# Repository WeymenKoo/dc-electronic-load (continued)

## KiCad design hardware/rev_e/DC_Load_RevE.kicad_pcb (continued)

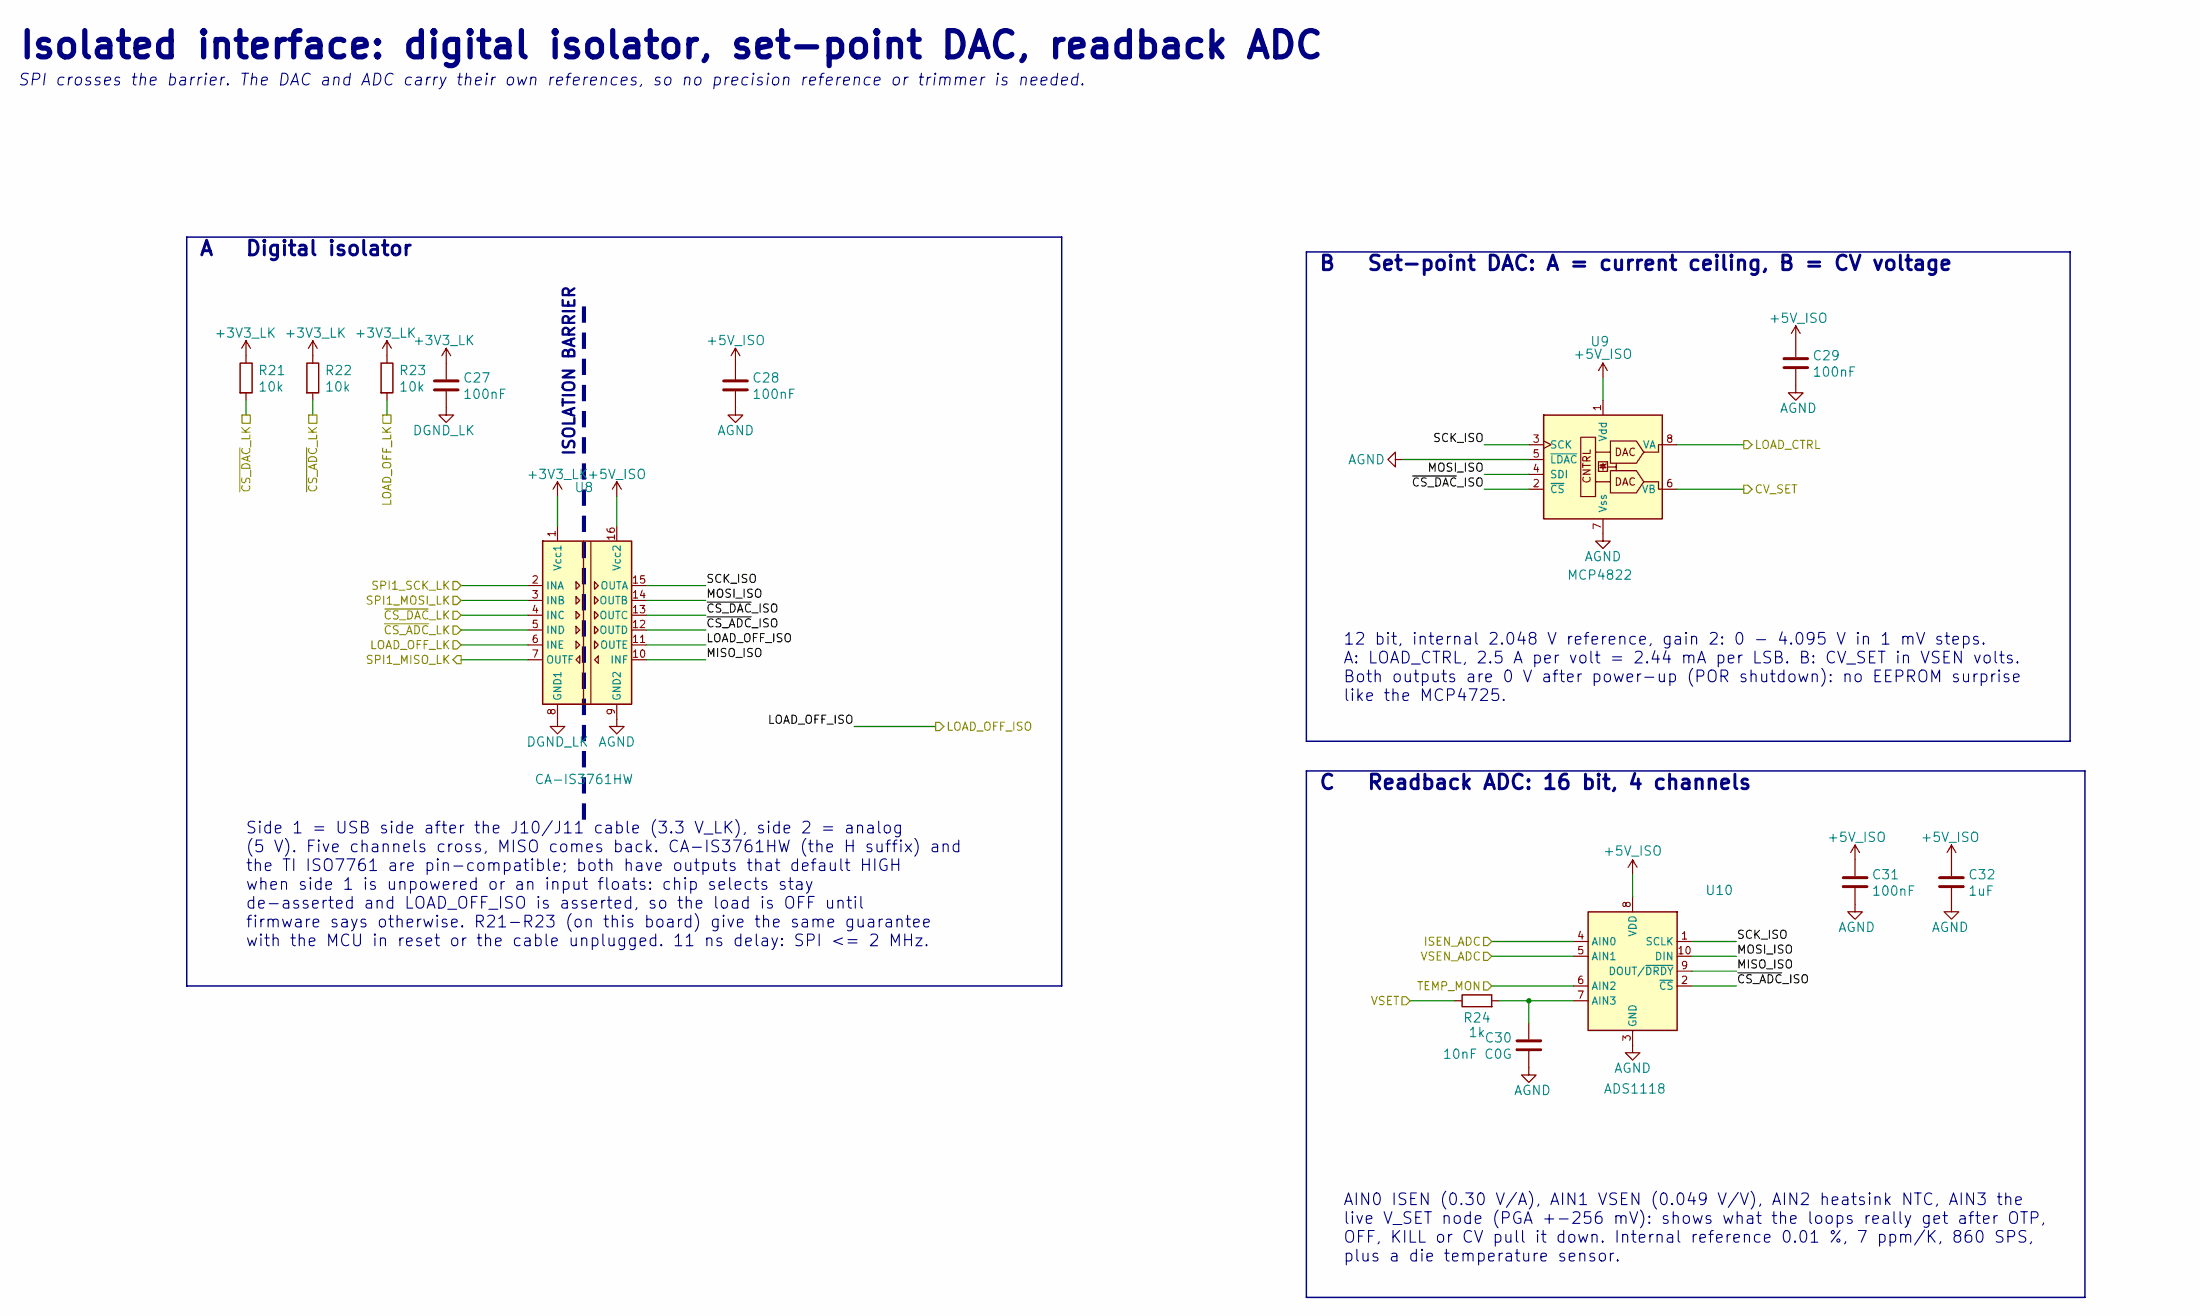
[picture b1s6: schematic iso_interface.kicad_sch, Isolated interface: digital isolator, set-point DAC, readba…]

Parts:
C27, C28, C29, C31: 100nF; C_0603_1608Metric
C30: 10nF C0G; C_0603_1608Metric
C32: 1uF; C_0603_1608Metric
R21, R22, R23: 10k; R_0603_1608Metric
R24: 1k; R_0603_1608Metric
U8: CA-IS3761HW; SOIC-16W_7.5x10.3mm_P1.27mm; MPN Chipanalog CA-IS3761HW, 5 kVrms, defaul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; LCSC C528656
U9: MCP4822; SOIC-8_3.9x4.9mm_P1.27mm; MPN MCP4822-E/SN; LCSC C16040
U10: ADS1118; TSSOP-10_3x3mm_P0.5mm; MPN ADS1118IDGSR; LCSC C55347

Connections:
+3V3_LK: C27.1, R21.1, R22.1, R23.1, U8.1 (Vcc1); also elsewhere on the board
+5V_ISO: C28.1, C29.1, C31.1, C32.1, U8.16 (Vcc2), U9.1 (Vdd), U10.8 (VDD); also elsewhere on the board
/Board Link/LOAD_OFF_LK: R23.2, U8.6 (INE); also elsewhere on the board
/Board Link/SPI1_MISO_LK: U8.7 (OUTF); also elsewhere on the board
/Board Link/SPI1_MOSI_LK: U8.3 (INB); also elsewhere on the board
/Board Link/SPI1_SCK_LK: U8.2 (INA); also elsewhere on the board
/Board Link/~CS_ADC_LK: R22.2, U8.5 (IND); also elsewhere on the board
/Board Link/~CS_DAC_LK: R21.2, U8.4 (INC); also elsewhere on the board
/Channel 1/VSET: R24.1; also elsewhere on the board
/Isolated Interface/CV_SET: U9.6 (VB); also elsewhere on the board
/Isolated Interface/ISEN_ADC: U10.4 (AIN0); also elsewhere on the board
/Isolated Interface/LOAD_CTRL: U9.8 (VA); also elsewhere on the board
/Isolated Interface/LOAD_OFF_ISO: U8.11 (OUTE); also elsewhere on the board
/Isolated Interface/MISO_ISO: U8.10 (INF), U10.9 (DOUT/~DRDY)
/Isolated Interface/MOSI_ISO: U8.14 (OUTB), U9.4 (SDI), U10.10 (DIN)
/Isolated Interface/SCK_ISO: U8.15 (OUTA), U9.3 (SCK), U10.1 (SCLK)
/Isolated Interface/TEMP_MON: U10.6 (AIN2); also elsewhere on the board
/Isolated Interface/VSEN_ADC: U10.5 (AIN1); also elsewhere on the board
/Isolated Interface/~CS_ADC_ISO: U8.12 (OUTD), U10.2 (~CS)
/Isolated Interface/~CS_DAC_ISO: U8.13 (OUTC), U9.2 (~CS)
AGND: C28.2, C29.2, C30.2, C31.2, C32.2, U8.9 (GND2), U9.5 (~LDAC), U9.7 (Vss), U10.3 (GND); also elsewhere on the board
DGND_LK: C27.2, U8.8 (GND1); also elsewhere on the board
unnamed: C30.1, R24.2, U10.7 (AIN3)

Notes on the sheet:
Isolated interface: digital isolator, set-point DAC, readback ADC
SPI crosses the barrier. The DAC and ADC carry their own references, so no precision reference or trimmer is needed.
ISOLATION BARRIER
Side 1 = USB side after the J10/J11 cable (3.3 V_LK), side 2 = analog (5 V). Five channels cross, MISO comes back. CA-IS3761HW (the H suffix) and the TI ISO7761 are pin-compatible; both have outputs that default HIGH when side 1 is unpowered or an input floats: chip selects stay de-asserted and LOA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
A Digital isolator
12 bit, internal 2.048 V reference, gain 2: 0 - 4.095 V in 1 mV steps. A: LOAD_CTRL, 2.5 A per volt = 2.44 mA per LSB. B: CV_SET in VSEN volts. Both outputs are 0 V after power-up (POR shutdown): no EEPROM surprise like the MCP4725.
B Set-point DAC: A = current ceiling, B = CV voltage
AIN0 ISEN (0.30 V/A), AIN1 VSEN (0.049 V/V), AIN2 heatsink NTC, AIN3 the live V_SET node (PGA +-256 mV): shows what the loops really get after OTP, OFF, KILL or CV pull it down. Internal reference 0.01 %, 7 ppm/K, 860 SPS, plus a die temperature sensor.
C Readback ADC: 16 bit, 4 channels

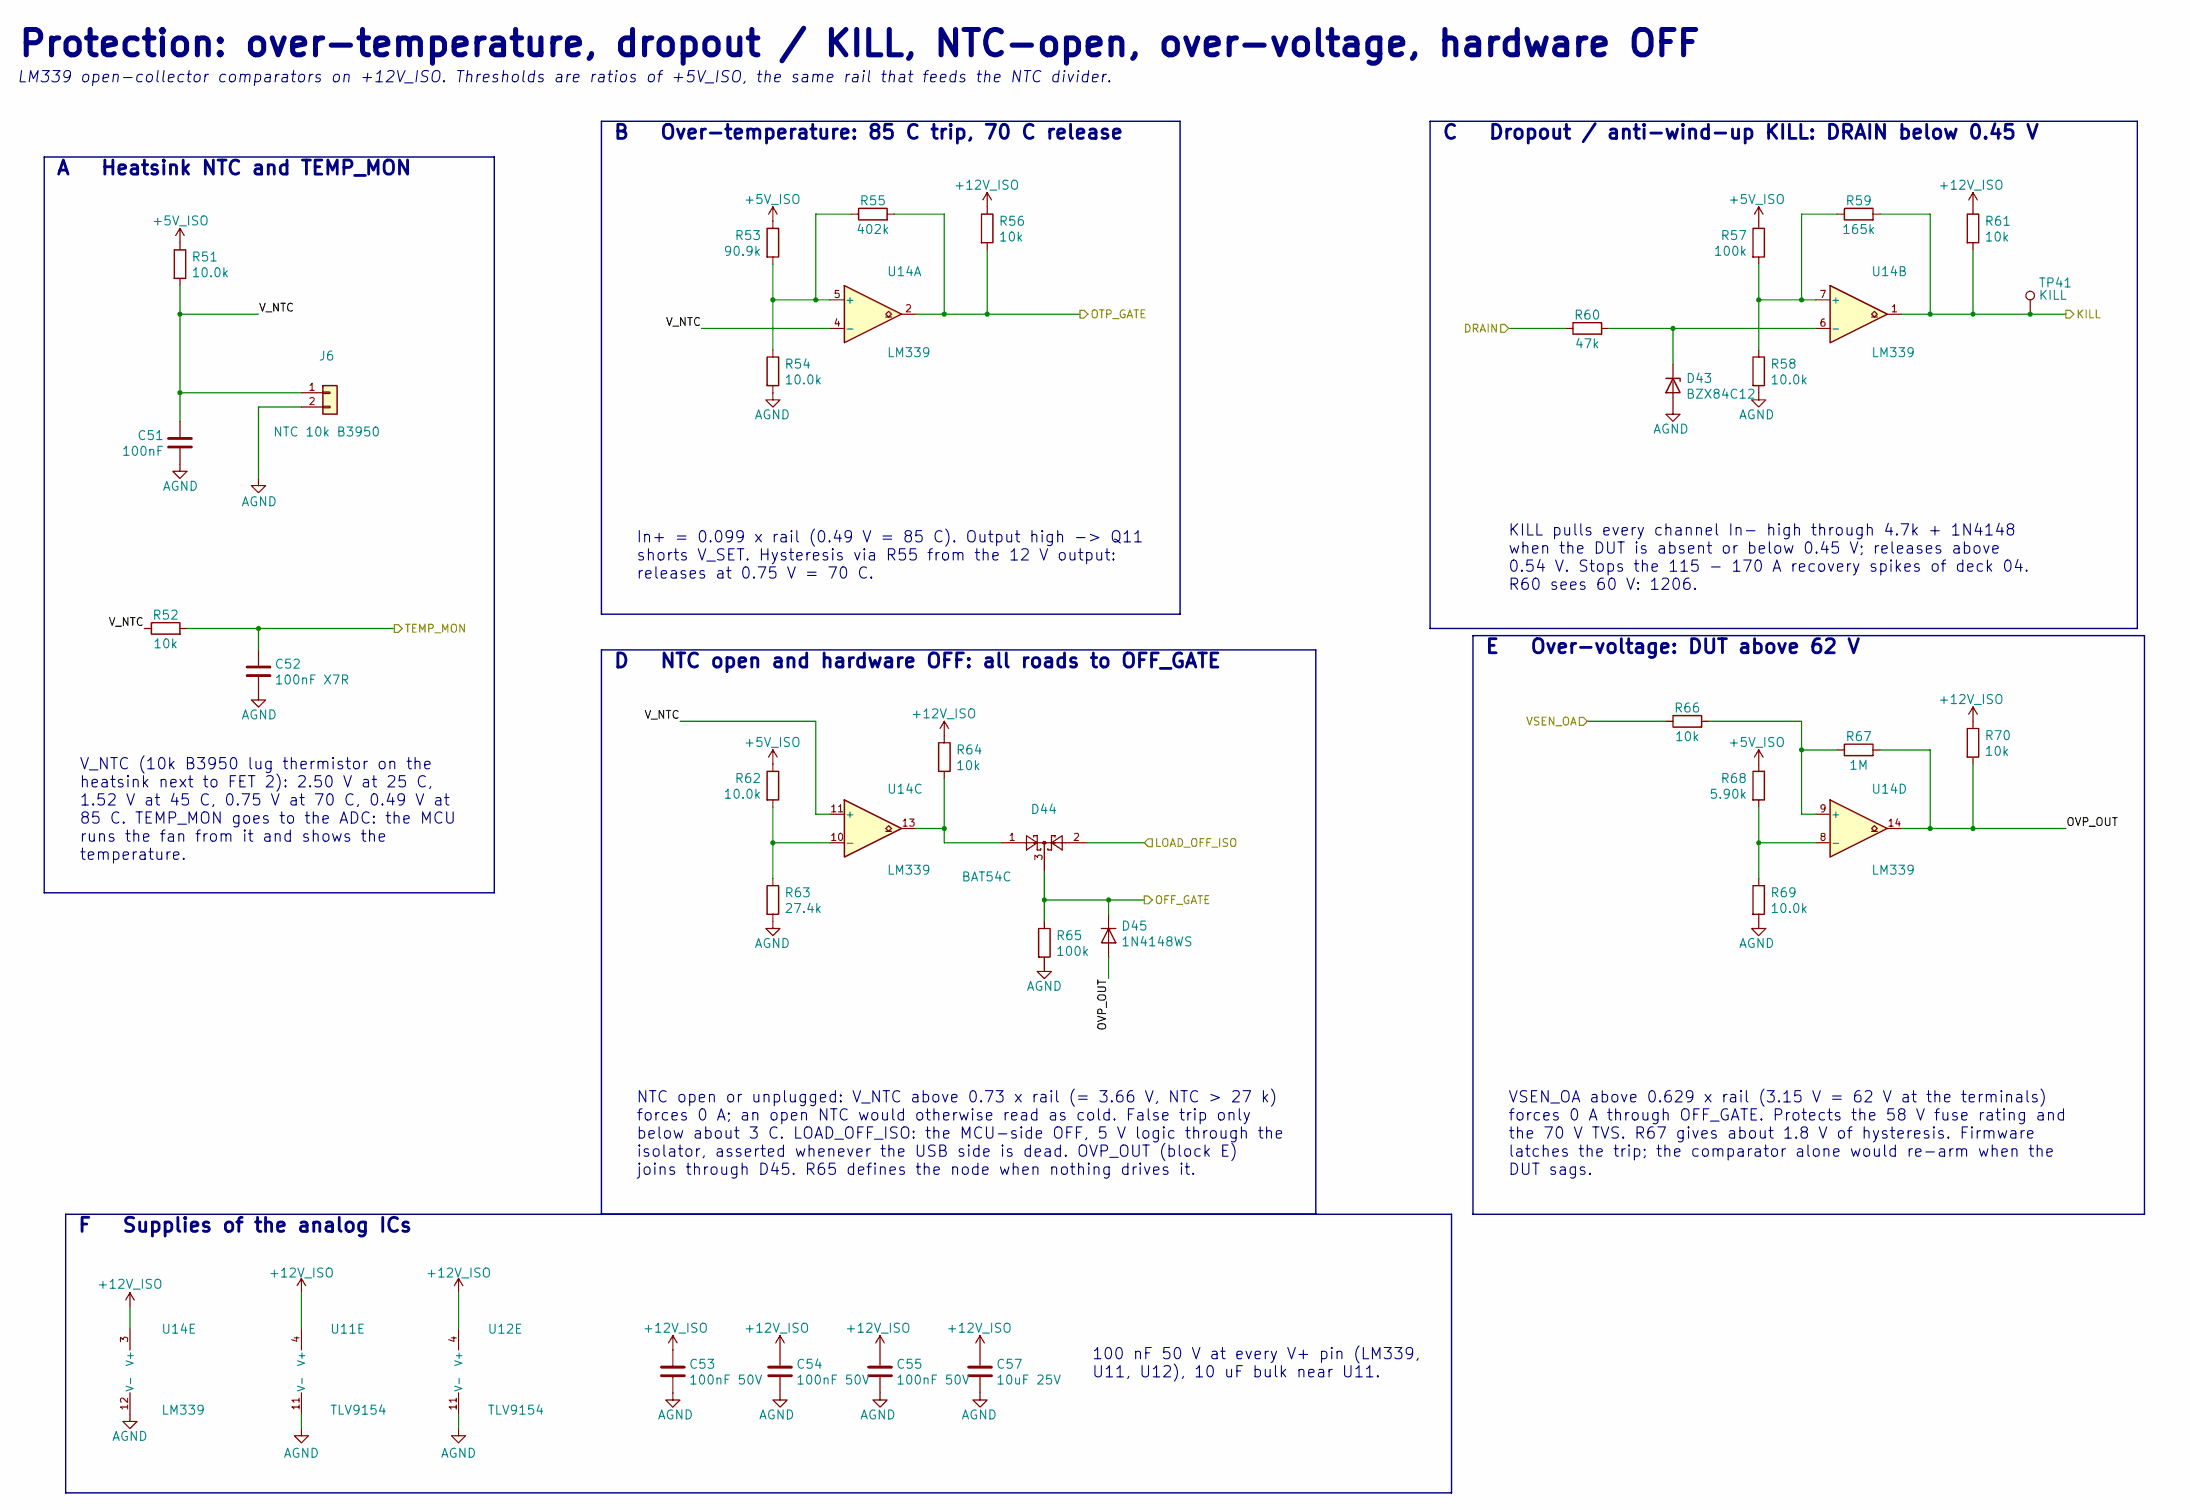
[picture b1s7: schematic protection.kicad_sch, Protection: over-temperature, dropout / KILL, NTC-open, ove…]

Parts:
C51: 100nF; C_0603_1608Metric
C52: 100nF X7R; C_0603_1608Metric
C53, C54, C55: 100nF 50V; C_0603_1608Metric
C57: 10uF 25V; C_0805_2012Metric
D43: BZX84C12; SOT-23; LCSC C118577
D44: BAT54C; SOT-23; LCSC C2135
D45: 1N4148WS; D_SOD-323; LCSC C2128
J6: NTC 10k B3950; JST_XH_B2B-XH-A_1x02_P2.50mm_Vertical; MPN JST B2B-XH-A(LF)(SN); NTC = 10k B3950 r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; LCSC C158012
R51, R54, R58, R62, R69: 10.0k; R_0603_1608Metric; Tolerance 1%
R52, R56, R61, R64, R70: 10k; R_0603_1608Metric
R53: 90.9k; R_0603_1608Metric; Tolerance 1%
R55: 402k; R_0603_1608Metric; Tolerance 1%
R57: 100k; R_0603_1608Metric; Tolerance 1%
R59: 165k; R_0603_1608Metric; Tolerance 1%
R60: 47k; R_1206_3216Metric; Tolerance 1%; LCSC C102201
R63: 27.4k; R_0603_1608Metric; Tolerance 1%
R65: 100k; R_0603_1608Metric
R66: 10k; R_0603_1608Metric; Tolerance 1%
R67: 1M; R_0603_1608Metric; Tolerance 1%
R68: 5.90k; R_0603_1608Metric; Tolerance 1%
TP41: KILL; TestPoint_THTPad_D1.5mm_Drill0.7mm
U11, U12: TLV9154; SOIC-14_3.9x8.7mm_P1.27mm; MPN TLV9154IDR; LCSC C2873614
U14: LM339; SOIC-14_3.9x8.7mm_P1.27mm; MPN LM339DR; LCSC C5236695

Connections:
+5V_ISO: R51.1, R53.1, R57.1, R62.1, R68.1; also elsewhere on the board
+12V_ISO: C53.1, C54.1, C55.1, C57.1, R56.1, R61.1, R64.1, R70.1, U11.4 (V+), U12.4 (V+), U14.3 (V+); also elsewhere on the board
/Channel 1/DRAIN: R60.1; also elsewhere on the board
/Channel 1/KILL: R59.2, R61.2, TP41.1, U14.1; also elsewhere on the board
/Channel 1/VSET: U11.5 (+), U11.10 (+), U11.12 (+); also elsewhere on the board
/Isolated Interface/LOAD_OFF_ISO: D44.2; also elsewhere on the board
/Isolated Interface/TEMP_MON: C52.1, R52.2; also elsewhere on the board
/Protection/OFF_GATE: D44.3, D45.1 (K), R65.1; also elsewhere on the board
/Protection/OTP_GATE: R55.2, R56.2, U14.2; also elsewhere on the board
/Protection/OVP_OUT: D45.2 (A), R67.2, R70.2, U14.14
/Protection/VSEN_OA: R66.1; also elsewhere on the board
/Protection/V_NTC: C51.1, J6.1, R51.2, R52.1, U14.4 (-), U14.11 (+)
AGND: C51.2, C52.2, C53.2, C54.2, C55.2, C57.2, D43.1 (A), J6.2, R54.2, R58.2, R63.2, R65.2, R69.2, U11.11 (V-), U12.11 (V-), U14.12 (V-); also elsewhere on the board
unnamed: D43.3 (K), R60.2, U14.6 (-)
unnamed: D44.1, R64.2, U14.13
unnamed 82: U11.6 (-); also elsewhere on the board
unnamed 83: U11.7; also elsewhere on the board
unnamed 87: U11.9 (-); also elsewhere on the board
unnamed 88: U11.8; also elsewhere on the board
unnamed 92: U11.13 (-); also elsewhere on the board
unnamed 93: U11.14; also elsewhere on the board
unnamed: R53.2, R54.1, R55.1, U14.5 (+)
unnamed: R57.2, R58.1, R59.1, U14.7 (+)
unnamed: R62.2, R63.1, U14.10 (-)
unnamed: R66.2, R67.1, U14.9 (+)
unnamed: R68.2, R69.1, U14.8 (-)

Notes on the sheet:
Protection: over-temperature, dropout / KILL, NTC-open, over-voltage, hardware OFF
LM339 open-collector comparators on +12V_ISO. Thresholds are ratios of +5V_ISO, the same rail that feeds the NTC divider.
V_NTC (10k B3950 lug thermistor on the heatsink next to FET 2): 2.50 V at 25 C, 1.52 V at 45 C, 0.75 V at 70 C, 0.49 V at 85 C. TEMP_MON goes to the ADC: the MCU runs the fan from it and shows the temperature.
A Heatsink NTC and TEMP_MON
In+ = 0.099 x rail (0.49 V = 85 C). Output high -> Q11 shorts V_SET. Hysteresis via R55 from the 12 V output: releases at 0.75 V = 70 C.
B Over-temperature: 85 C trip, 70 C release
KILL pulls every channel In- high through 4.7k + 1N4148 when the DUT is absent or below 0.45 V; releases above 0.54 V. Stops the 115 - 170 A recovery spikes of deck 04. R60 sees 60 V: 1206.
C Dropout / anti-wind-up KILL: DRAIN below 0.45 V
NTC open or unplugged: V_NTC above 0.73 x rail (= 3.66 V, NTC > 27 k) forces 0 A; an open NTC would otherwise read as cold. False trip only below about 3 C. LOAD_OFF_ISO: the MCU-side OFF, 5 V logic through the isolator, asserted whenever the USB side is dead. OVP_OUT (block E) joins through D45. R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
D NTC open and hardware OFF: all roads to OFF_GATE
VSEN_OA above 0.629 x rail (3.15 V = 62 V at the terminals) forces 0 A through OFF_GATE. Protects the 58 V fuse rating and the 70 V TVS. R67 gives about 1.8 V of hysteresis. Firmware latches the trip; the comparator alone would re-arm when the DUT sags.
E Over-voltage: DUT above 62 V
100 nF 50 V at every V+ pin (LM339, U11, U12), 10 uF bulk near U11.
F Supplies of the analog ICs

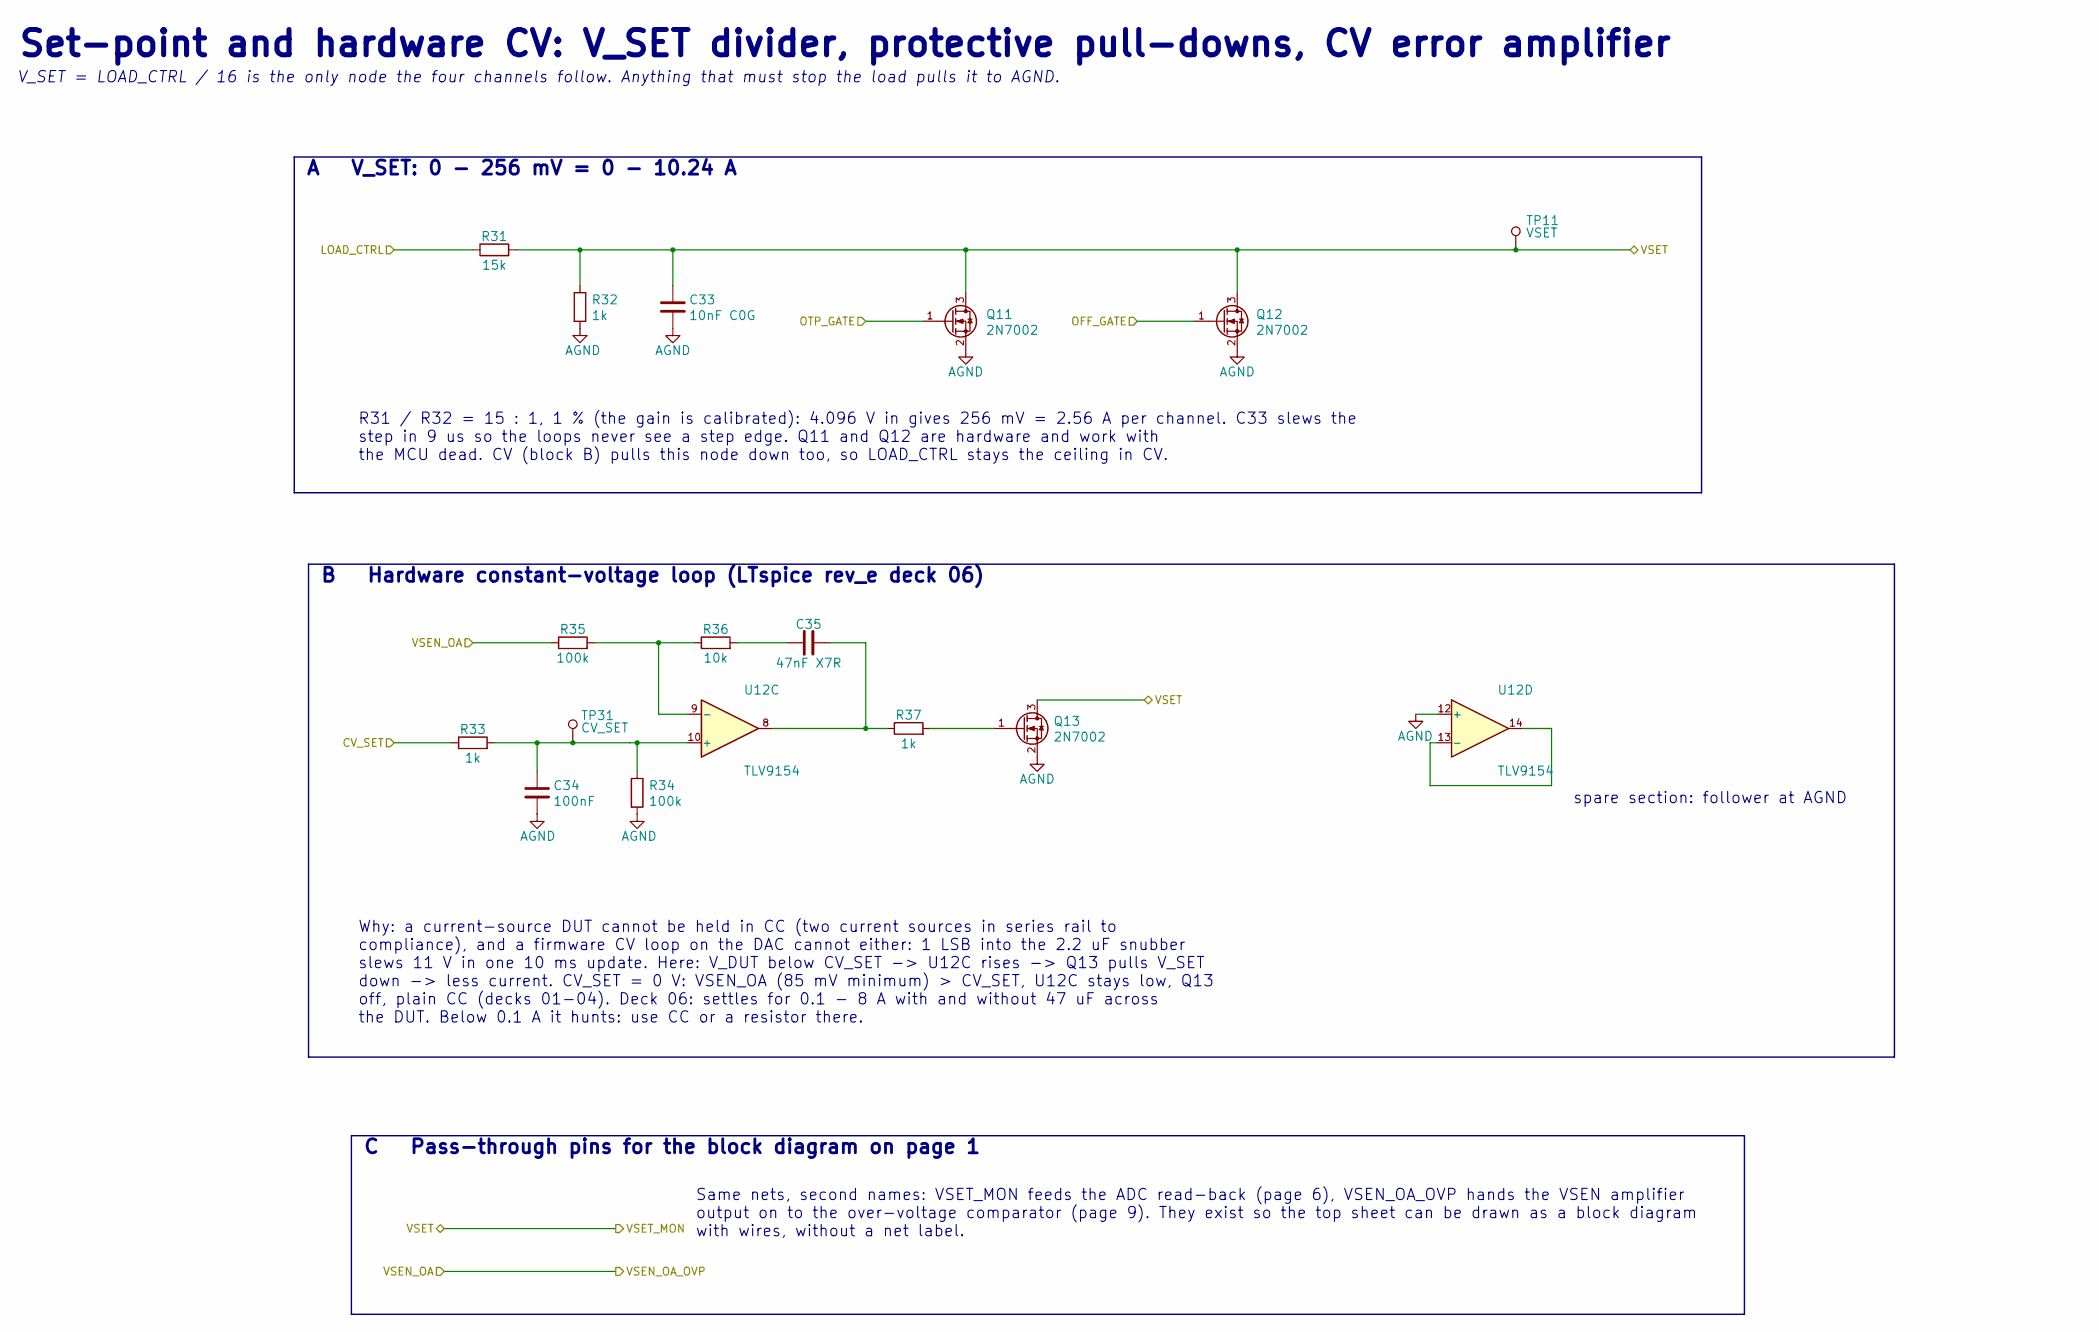
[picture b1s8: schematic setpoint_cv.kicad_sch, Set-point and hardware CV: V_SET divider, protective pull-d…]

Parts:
C33: 10nF C0G; C_0603_1608Metric
C34: 100nF; C_0603_1608Metric
C35: 47nF X7R; C_0603_1608Metric
Q11, Q12, Q13: 2N7002; SOT-23; LCSC C8545
R31: 15k; R_0603_1608Metric; Tolerance 1%
R32: 1k; R_0603_1608Metric; Tolerance 1%
R33, R37: 1k; R_0603_1608Metric
R34, R35: 100k; R_0603_1608Metric; Tolerance 1%
R36: 10k; R_0603_1608Metric; Tolerance 1%
TP11: VSET; TestPoint_THTPad_D1.5mm_Drill0.7mm
TP31: CV_SET; TestPoint_THTPad_D1.5mm_Drill0.7mm
U12: TLV9154; SOIC-14_3.9x8.7mm_P1.27mm; MPN TLV9154IDR; LCSC C2873614

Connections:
/Channel 1/VSET: C33.1, Q11.3 (D), Q12.3 (D), Q13.3 (D), R31.2, R32.1, TP11.1; also elsewhere on the board
/Isolated Interface/CV_SET: R33.1; also elsewhere on the board
/Isolated Interface/LOAD_CTRL: R31.1; also elsewhere on the board
/Protection/OFF_GATE: Q12.1 (G); also elsewhere on the board
/Protection/OTP_GATE: Q11.1 (G); also elsewhere on the board
/Protection/VSEN_OA: R35.1; also elsewhere on the board
AGND: C33.2, C34.2, Q11.2 (S), Q12.2 (S), Q13.2 (S), R32.2, R34.2, U12.12 (+); also elsewhere on the board
unnamed: C35.1, R36.2
unnamed: C35.2, R37.1, U12.8
unnamed: Q13.1 (G), R37.2
unnamed: C34.1, R33.2, R34.1, TP31.1, U12.10 (+)
unnamed: R35.2, R36.1, U12.9 (-)
unnamed: U12.13 (-), U12.14

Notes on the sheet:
Set-point and hardware CV: V_SET divider, protective pull-downs, CV error amplifier
V_SET = LOAD_CTRL / 16 is the only node the four channels follow. Anything that must stop the load pulls it to AGND.
R31 / R32 = 15 : 1, 1 % (the gain is calibrated): 4.096 V in gives 256 mV = 2.56 A per channel. C33 slews the step in 9 us so the loops never see a step edge. Q11 and Q12 are hardware and work with the MCU dead. CV (block B) pulls this node down too, so LOAD_CTRL stays the ceiling in CV.
A V_SET: 0 - 256 mV = 0 - 10.24 A
spare section: follower at AGND
Why: a current-source DUT cannot be held in CC (two current sources in series rail to compliance), and a firmware CV loop on the DAC cannot either: 1 LSB into the 2.2 uF snubber slews 11 V in one 10 ms update. Here: V_DUT below CV_SET -> U12C rises -> Q13 pulls V_SET down -> less current. CV_SET = 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
B Hardware constant-voltage loop (LTspice rev_e deck 06)
Same nets, second names: VSET_MON feeds the ADC read-back (page 6), VSEN_OA_OVP hands the VSEN amplifier output on to the over-voltage comparator (page 9). They exist so the top sheet can be drawn as a block diagram with wires, without a net label.
C Pass-through pins for the block diagram on page 1

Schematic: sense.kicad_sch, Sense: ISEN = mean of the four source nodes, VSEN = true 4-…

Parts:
C41, C42: 10nF C0G 50V; C_0603_1608Metric
D41, D42: BAT54S; SOT-23; LCSC C12765
R41: 1M; R_0603_1608Metric; Tolerance 1%
R42, R46, R49: 10k; R_0603_1608Metric; Tolerance 1%
R43: 110k; R_0603_1608Metric; Tolerance 1%
R44, R50: 1k; R_0603_1608Metric; Tolerance 1%
R45, R48: 200k; R_1206_3216Metric; Tolerance 1%; LCSC C17954
R47: 470k; R_0603_1608Metric; Tolerance 1%
TP21: ISEN_ADC; TestPoint_THTPad_D1.5mm_Drill0.7mm
TP22: VSEN_ADC; TestPoint_THTPad_D1.5mm_Drill0.7mm
U12: TLV9154; SOIC-14_3.9x8.7mm_P1.27mm; MPN TLV9154IDR; LCSC C2873614

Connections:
+5V_ISO: D41.2 (K), D42.2 (K), R41.1, R47.2; also elsewhere on the board
/Channel 1/AVG: R41.2, U12.3 (+); also elsewhere on the board
/Isolated Interface/ISEN_ADC: C41.1, D41.3 (COM), R44.2, TP21.1; also elsewhere on the board
/Isolated Interface/VSEN_ADC: C42.1, D42.3 (COM), R50.2, TP22.1; also elsewhere on the board
/Power Path/SENSE_N: R48.1; also elsewhere on the board
/Power Path/SENSE_P: R45.1; also elsewhere on the board
/Protection/VSEN_OA: R49.2, R50.1, U12.7; also elsewhere on the board
AGND: C41.2, C42.2, D41.1 (A), D42.1 (A), R42.2, R46.2; also elsewhere on the board
unnamed: R43.2, R44.1, U12.1
unnamed: R42.1, R43.1, U12.2 (-)
unnamed: R45.2, R46.1, R47.1, U12.5 (+)
unnamed: R48.2, R49.1, U12.6 (-)

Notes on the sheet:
Sense: ISEN = mean of the four source nodes, VSEN = true 4-wire difference amplifier
Both outputs are scaled for the 4.096 V ADC range and clamped to +5V_ISO. Offsets are deliberate and calibrated out in firmware.
Gain 12 (R43 / R42 + 1, 1 %: up to 2 % gain error, removed by the 2-point calibration). R41 injects +12 mV at the input (= +0.15 V out), kept from Rev C: a zero calibration removes it. Full scale 3.22 V at 10.24 A, 0.4 mA per ADS1118 LSB. U12A, standard quad pinout.
A ISEN: 0.300 V/A + 0.15 V
VSEN = 0.049 x (SENSE_P - SENSE_N) + 0.10 V: 2.5 mV of DUT per LSB, clips at 65 V. R45 and R48 see 60 V: 1206. 1 % resistors: up to 2 % gain error (calibrated out) and CMRR about 40 dB, harmless because SENSE_N sits within millivolts of AGND. R49 feeds back to -IN (Rev B had it on +IN and latched).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
B VSEN: 0.049 V/V + 0.10 V, true 4-wire

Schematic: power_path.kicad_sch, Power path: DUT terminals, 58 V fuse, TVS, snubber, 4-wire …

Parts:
C58: 2.2uF 100V X7R; C_1206_3216Metric; LCSC C170101
D51: SMCJ70A TVS; D_SMC; LCSC C2943781
F1: 15A 58VDC mini blade; Fuse_Blade_Mini_directSolder; MPN Littelfuse 0997015.WXN, soldered in (pl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; LCSC C207027
J7: DUT+; MountingHole_4.3mm_M4_Pad; MPN M4 x 12 bolt, nut, 2 washers (hardware 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
J8: DUT-; MountingHole_4.3mm_M4_Pad; MPN M4 x 12 bolt, nut, 2 washers (hardware 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
J9: SENSE; JST_XH_B2B-XH-A_1x02_P2.50mm_Vertical; MPN JST B2B-XH-A(LF)(SN); LCSC C158012
R71: 2.2R 1W; R_2512_6332Metric; Tolerance 5%; LCSC C25480
R72, R73: 100R; R_1206_3216Metric; LCSC C17901
TP51: DUT+; TestPoint_THTPad_D1.5mm_Drill0.7mm
TP52: DRAIN; TestPoint_THTPad_D1.5mm_Drill0.7mm

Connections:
/Channel 1/DRAIN: D51.1 (K), F1.2, R71.1, TP52.1; also elsewhere on the board
/Power Path/DUT_P: F1.1, J7.1, R72.1, TP51.1
/Power Path/SENSE_N: J9.2, R73.1; also elsewhere on the board
/Power Path/SENSE_P: J9.1, R72.2; also elsewhere on the board
unnamed: C58.1, R71.2
PGND: C58.2, D51.2 (A), J8.1, R73.2; also elsewhere on the board

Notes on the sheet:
Power path: DUT terminals, 58 V fuse, TVS, snubber, 4-wire sense
DUT+ -> fuse -> DRAIN bus -> four drains. The source resistors return to PGND, which meets AGND only at NT1.
Fuse: the 58 V DC MINI part named, soldered into the direct-solder footprint (a blown fuse means a shorted FET, so it is replaced on the bench anyway). Ordinary blade fuses are rated 32 V, so 58 V is the DUT limit of this board (OVP trips at 62 V). No series diode, so the load works down to 0.6 V. 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
A Terminals and DRAIN bus
J9 open: R72 / R73 connect the sense amplifier to the terminals. J9 wired to the DUT: they carry only microamps and the lead drop leaves the reading. A miswired sense lead burns a 100 R 1206 open and nothing else.
B 4-wire sense with local fallback

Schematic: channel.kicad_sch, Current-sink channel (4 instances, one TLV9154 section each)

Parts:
C01: 1nF C0G 50V; C_0603_1608Metric
D01: 1N4148WS; D_SOD-323; LCSC C2128
D02: BZX84C6V8; SOT-23; LCSC C118571
D03: BZX84C15; SOT-23; LCSC C328579
Q01: IRFP250NPBF; TO-247-3_Vertical; MPN IRFP250NPBF (Infineon, LCSC C2580; not 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; LCSC C2580
R01: 4.7k; R_0603_1608Metric; Tolerance 1%
R02: 15M; R_0603_1608Metric; Tolerance 5%
R03: 3.3k; R_0603_1608Metric; Tolerance 1%
R04: 47; R_0603_1608Metric; Tolerance 1%
R05: 100k; R_0603_1608Metric
R06, R07: 0R2 2W; R_2512_6332Metric; Tolerance 1%; LCSC C5375444
R08: 10k; R_0603_1608Metric; Tolerance 1%
TP01: GATE; TestPoint_THTPad_D1.5mm_Drill0.7mm
TP02: SOURCE; TestPoint_THTPad_D1.5mm_Drill0.7mm
U11: TLV9154; SOIC-14_3.9x8.7mm_P1.27mm; MPN TLV9154IDR; LCSC C2873614

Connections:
/Channel 1/VSET: U11.3 (+), U11.5 (+), U11.10 (+), U11.12 (+); also elsewhere on the board
unnamed 77: U11.2 (-); also elsewhere on the board
unnamed 78: U11.1; also elsewhere on the board
unnamed 82: U11.6 (-); also elsewhere on the board
unnamed 83: U11.7; also elsewhere on the board
unnamed 87: U11.9 (-); also elsewhere on the board
unnamed 88: U11.8; also elsewhere on the board
unnamed 92: U11.13 (-); also elsewhere on the board
unnamed 93: U11.14; also elsewhere on the board

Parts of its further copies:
C101, C201, C301, C401: 1nF C0G 50V; C_0603_1608Metric
D101, D201, D301, D401: 1N4148WS; D_SOD-323; LCSC C2128
D102, D202, D302, D402: BZX84C6V8; SOT-23; LCSC C118571
D103, D203, D303, D403: BZX84C15; SOT-23; LCSC C328579
Q101, Q201, Q301, Q401: IRFP250NPBF; TO-247-3_Vertical; MPN IRFP250NPBF (Infineon, LCSC C2580; not 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; LCSC C2580
R101, R201, R301, R401: 4.7k; R_0603_1608Metric; Tolerance 1%
R102, R202, R302, R402: 15M; R_0603_1608Metric; Tolerance 5%
R103, R203, R303, R403: 3.3k; R_0603_1608Metric; Tolerance 1%
R104, R204, R304, R404: 47; R_0603_1608Metric; Tolerance 1%
R105, R205, R305, R405: 100k; R_0603_1608Metric
R106, R107, R206, R207, R306, R307, R406, R407: 0R2 2W; R_2512_6332Metric; Tolerance 1%; LCSC C5375444
R108, R208, R308, R408: 10k; R_0603_1608Metric; Tolerance 1%
TP101, TP201, TP301, TP401: GATE; TestPoint_THTPad_D1.5mm_Drill0.7mm
TP102, TP202, TP302, TP402: SOURCE; TestPoint_THTPad_D1.5mm_Drill0.7mm

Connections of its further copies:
+12V_ISO: R102.1, R202.1, R302.1, R402.1; also elsewhere on the board
/Channel 1/AVG: R108.2, R208.2, R308.2, R408.2; also elsewhere on the board
/Channel 1/DRAIN: Q101.2 (D), Q201.2 (D), Q301.2 (D), Q401.2 (D); also elsewhere on the board
/Channel 1/KILL: R101.1, R201.1, R301.1, R401.1; also elsewhere on the board
unnamed: D101.2 (A), R101.2
unnamed 77: C101.1, D101.1 (K), D102.1 (A), R102.2, R103.1; also elsewhere on the board
unnamed 78: C101.2, D102.3 (K), R104.1; also elsewhere on the board
unnamed: D103.1 (A), Q101.3 (S), R103.2, R105.2, R106.1, R107.1, R108.1, TP102.1
unnamed: D103.3 (K), Q101.1 (G), R104.2, R105.1, TP101.1
unnamed: D201.2 (A), R201.2
unnamed 82: C201.1, D201.1 (K), D202.1 (A), R202.2, R203.1; also elsewhere on the board
unnamed 83: C201.2, D202.3 (K), R204.1; also elsewhere on the board
unnamed: D203.1 (A), Q201.3 (S), R203.2, R205.2, R206.1, R207.1, R208.1, TP202.1
unnamed: D203.3 (K), Q201.1 (G), R204.2, R205.1, TP201.1
unnamed: D301.2 (A), R301.2
unnamed 87: C301.1, D301.1 (K), D302.1 (A), R302.2, R303.1; also elsewhere on the board
unnamed 88: C301.2, D302.3 (K), R304.1; also elsewhere on the board
unnamed: D303.1 (A), Q301.3 (S), R303.2, R305.2, R306.1, R307.1, R308.1, TP302.1
unnamed: D303.3 (K), Q301.1 (G), R304.2, R305.1, TP301.1
unnamed: D401.2 (A), R401.2
unnamed 92: C401.1, D401.1 (K), D402.1 (A), R402.2, R403.1; also elsewhere on the board
unnamed 93: C401.2, D402.3 (K), R404.1; also elsewhere on the board
unnamed: D403.1 (A), Q401.3 (S), R403.2, R405.2, R406.1, R407.1, R408.1, TP402.1
unnamed: D403.3 (K), Q401.1 (G), R404.2, R405.1, TP401.1
PGND: R106.2, R107.2, R206.2, R207.2, R306.2, R307.2, R406.2, R407.2; also elsewhere on the board

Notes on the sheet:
Current-sink channel (4 instances, one TLV9154 section each)
Each MOSFET gets its own loop forced to V_SET / 0.1 R, so current and power share equally whatever the threshold spread.
Rs: two 0.2 R 2512 in parallel = 0.1 R, so I_ch = V_SET / 0.1 R (2.56 A full scale). KELVIN: Rn03 and Rn08 connect at the TOP PAD of the Rs pair on their own trace, never along the high-current source copper. Rg within 10 mm of the gate pin. Dn03 and Rn05 sit at the FET pins. Dn02 limits integrator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
Channel (one of four): TLV9154 section, 3.3k / 1n / 47R compensation, IRFP250N, 2 x 0.2R Kelvin sense
Same nets, second names (KILL_T = KILL ...). Channel 4 leaves KILL_T, VSET_T and AVG_T open; its DRAIN_T carries DRAIN on to the dropout comparator. Electrically every channel still hangs directly on the four nets.
Chain pins: the four channels are daisy-chained on page 1 (each net enters on the left and leaves on the right)
